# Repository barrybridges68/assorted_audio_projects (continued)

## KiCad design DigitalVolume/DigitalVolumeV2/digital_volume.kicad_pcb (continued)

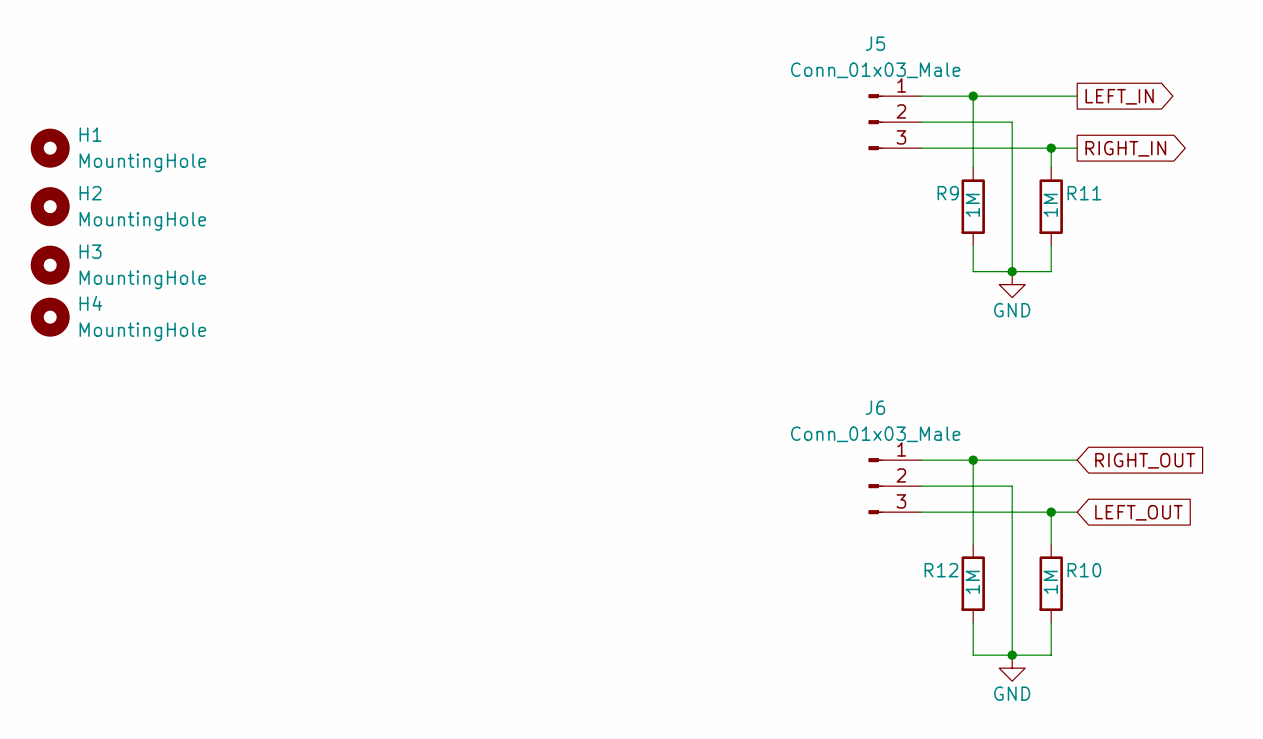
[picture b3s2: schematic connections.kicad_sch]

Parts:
H1, H2, H3, H4: MountingHole; MountingHole_3.2mm_M3
J5, J6: Conn_01x03_Male; TerminalBlock_Phoenix_MKDS-1,5-3-5.08_1x03_P5.08mm_Horizont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
R9, R10, R11, R12: 1M; R_0603_1608Metric

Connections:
GND: J5.2, J6.2, R9.2, R10.2, R11.2, R12.2; also elsewhere on the board
LEFT_IN: J5.1, R9.1; also elsewhere on the board
LEFT_OUT: J6.3, R10.1; also elsewhere on the board
RIGHT_IN: J5.3, R11.1; also elsewhere on the board
RIGHT_OUT: J6.1, R12.1; also elsewhere on the board

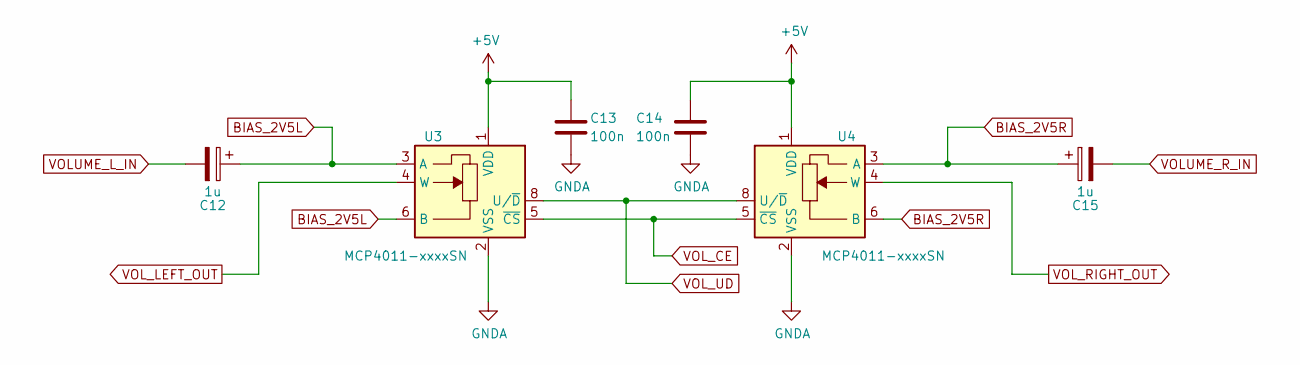
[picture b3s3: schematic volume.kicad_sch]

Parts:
C12, C15: 1u; CP_Elec_4x5.4
C13, C14: 100n; C_0603_1608Metric
U3, U4: MCP4011-xxxxSN; SOIC-8_3.9x4.9mm_P1.27mm

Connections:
+5V: C13.1, C14.1, U3.1 (VDD), U4.1 (VDD); also elsewhere on the board
BIAS_2V5L: C12.1, U3.3 (A), U3.6 (B); also elsewhere on the board
BIAS_2V5R: C15.1, U4.3 (A), U4.6 (B); also elsewhere on the board
GND: C13.2, C14.2, U3.2 (VSS), U4.2 (VSS); also elsewhere on the board
VOLUME_L_IN: C12.2; also elsewhere on the board
VOLUME_R_IN: C15.2; also elsewhere on the board
VOL_CE: U3.5 (~CS), U4.5 (~CS); also elsewhere on the board
VOL_LEFT_OUT: U3.4 (W); also elsewhere on the board
VOL_RIGHT_OUT: U4.4 (W); also elsewhere on the board
VOL_UD: U3.8 (U/~D), U4.8 (U/~D); also elsewhere on the board

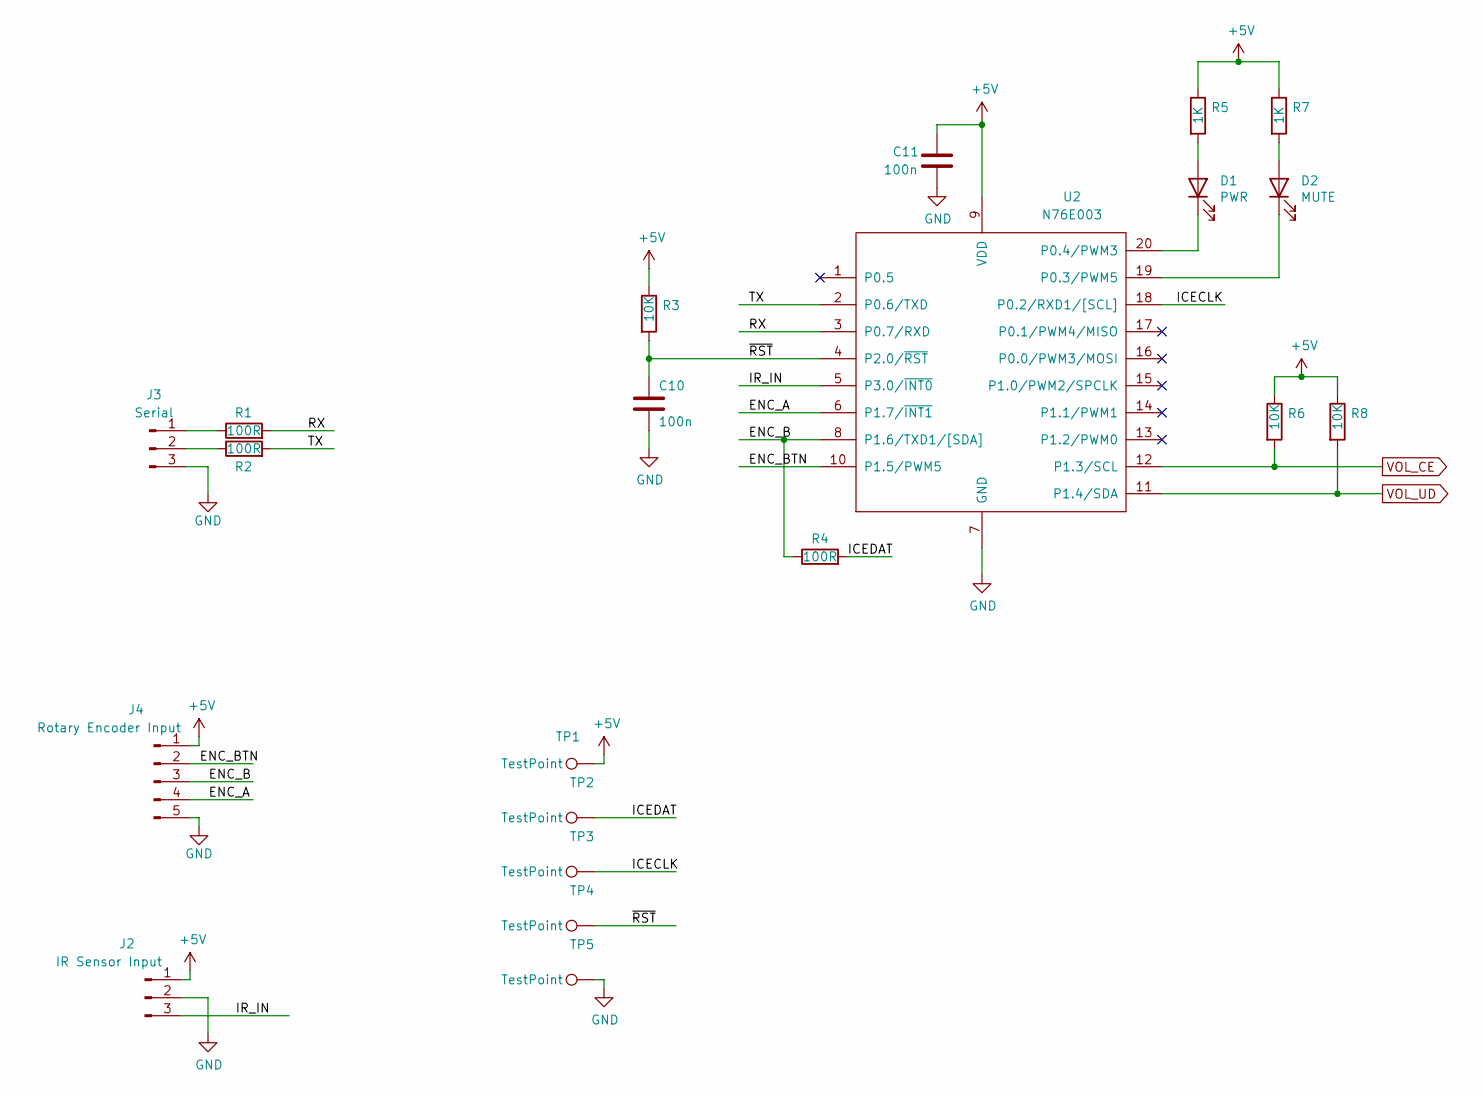
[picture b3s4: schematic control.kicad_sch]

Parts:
C10, C11: 100n; C_0603_1608Metric
D1: PWR; LED_0603_1608Metric_Pad1.05x0.95mm_HandSolder
D2: MUTE; LED_0603_1608Metric_Pad1.05x0.95mm_HandSolder
J2: IR Sensor Input; JST_EH_B3B-EH-A_1x03_P2.50mm_Vertical
J3: Serial; JST_EH_B3B-EH-A_1x03_P2.50mm_Vertical
J4: Rotary Encoder Input; JST_EH_B5B-EH-A_1x05_P2.50mm_Vertical
R1, R2, R4: 100R; R_0603_1608Metric
R3, R6, R8: 10K; R_0603_1608Metric
R5, R7: 1K; R_0603_1608Metric
TP1, TP2, TP3, TP4, TP5: TestPoint; TestPoint_Pad_1.0x1.0mm
U2: N76E003; TSSOP-20_4.4x6.5mm_P0.65mm

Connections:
+5V: C11.1, J2.1, J4.1, R3.1, R5.1, R6.1, R7.1, R8.1, TP1.1, U2.9 (VDD); also elsewhere on the board
/control/ENC_A: J4.4, U2.6 (P1.7/~INT1)
/control/ENC_B: J4.3, R4.1, U2.8 (P1.6/TXD1/[SDA])
/control/ENC_BTN: J4.2, U2.10 (P1.5/PWM5)
/control/ICECLK: TP3.1, U2.18 (P0.2/RXD1/[SCL])
/control/ICEDAT: R4.2, TP2.1
/control/IR_IN: J2.3, U2.5 (P3.0/~INT0)
/control/RX: R1.2, U2.3 (P0.7/RXD)
/control/TX: R2.2, U2.2 (P0.6/TXD)
/control/~RST: C10.1, R3.2, TP4.1, U2.4 (P2.0/~RST)
GND: C10.2, C11.2, J2.2, J3.3, J4.5, TP5.1, U2.7 (GND); also elsewhere on the board
unnamed: D1.1 (K), U2.20 (P0.4/PWM3)
unnamed: D1.2 (A), R5.2
unnamed: D2.1 (K), U2.19 (P0.3/PWM5)
unnamed: D2.2 (A), R7.2
unnamed: J3.1, R1.1
unnamed: J3.2, R2.1
VOL_CE: R6.2, U2.12 (P1.3/SCL); also elsewhere on the board
VOL_UD: R8.2, U2.11 (P1.4/SDA); also elsewhere on the board

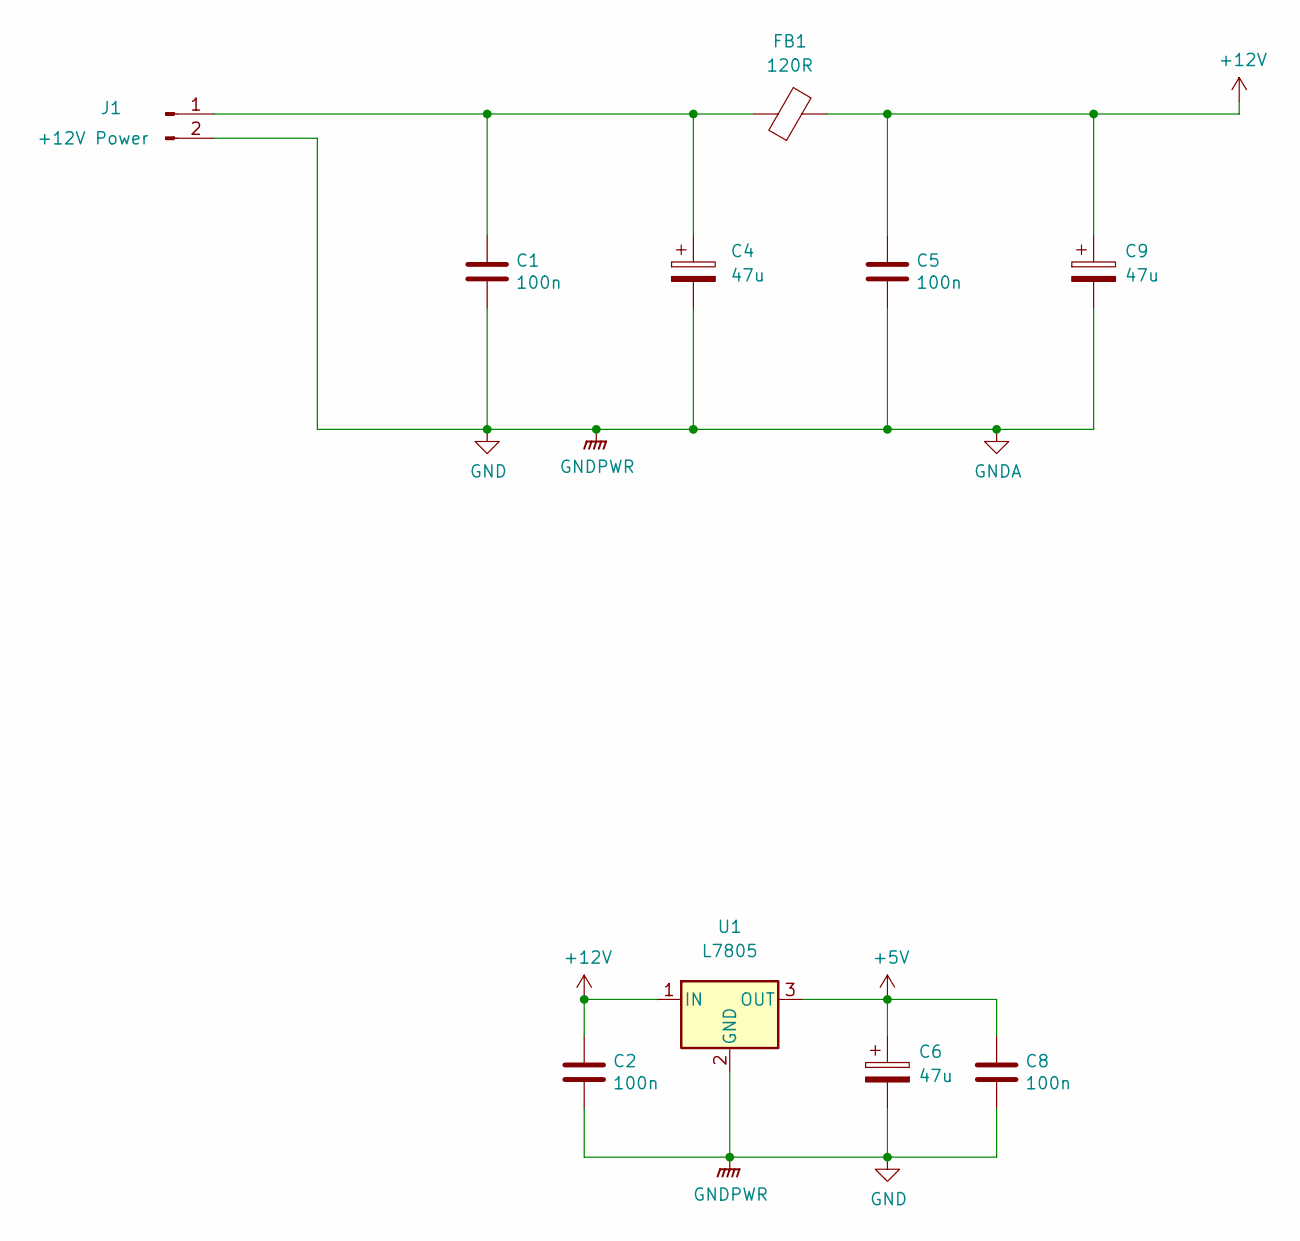
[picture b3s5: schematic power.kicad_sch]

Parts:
C1, C2, C5, C8: 100n; C_0603_1608Metric
C4, C6, C9: 47u; CP_Elec_6.3x5.3
FB1: 120R; R_0603_1608Metric
J1: +12V Power; TerminalBlock_Phoenix_MKDS-1,5-2_1x02_P5.00mm_Horizontal
U1: L7805; TO-252-2

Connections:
+5V: C6.1, C8.1, U1.3 (OUT); also elsewhere on the board
+12V: C2.1, C5.1, C9.1, FB1.2, U1.1 (IN); also elsewhere on the board
GND: C1.2, C2.2, C4.2, C5.2, C6.2, C8.2, C9.2, J1.2, U1.2 (GND); also elsewhere on the board
unnamed: C1.1, C4.1, FB1.1, J1.1

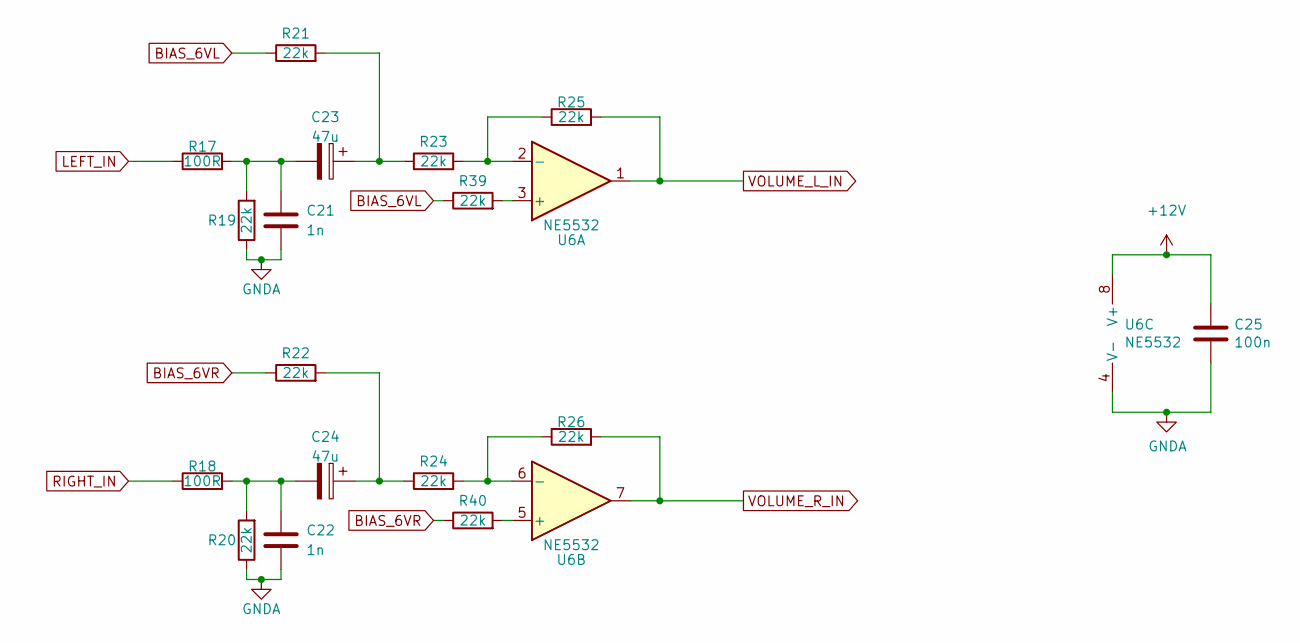
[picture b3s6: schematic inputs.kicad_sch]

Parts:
C21, C22: 1n; C_0603_1608Metric
C23, C24: 47u; CP_Elec_6.3x5.3
C25: 100n; C_0603_1608Metric
R17, R18: 100R; R_0603_1608Metric
R19, R20, R21, R22, R23, R24, R25, R26, R39, R40: 22k; R_0603_1608Metric
U6: NE5532; SOIC-8_3.9x4.9mm_P1.27mm

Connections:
+12V: C25.1, U6.8 (V+); also elsewhere on the board
BIAS_6VL: R21.1, R39.1; also elsewhere on the board
BIAS_6VR: R22.1, R40.1; also elsewhere on the board
GND: C21.2, C22.2, C25.2, R19.1, R20.1, U6.4 (V-); also elsewhere on the board
LEFT_IN: R17.1; also elsewhere on the board
unnamed: C21.1, C23.2, R17.2, R19.2
unnamed: C22.1, C24.2, R18.2, R20.2
unnamed: C23.1, R21.2, R23.1
unnamed: C24.1, R22.2, R24.1
unnamed: R23.2, R25.1, U6.2 (-)
unnamed: R24.2, R26.1, U6.6 (-)
unnamed: R39.2, U6.3 (+)
unnamed: R40.2, U6.5 (+)
RIGHT_IN: R18.1; also elsewhere on the board
VOLUME_L_IN: R25.2, U6.1; also elsewhere on the board
VOLUME_R_IN: R26.2, U6.7; also elsewhere on the board

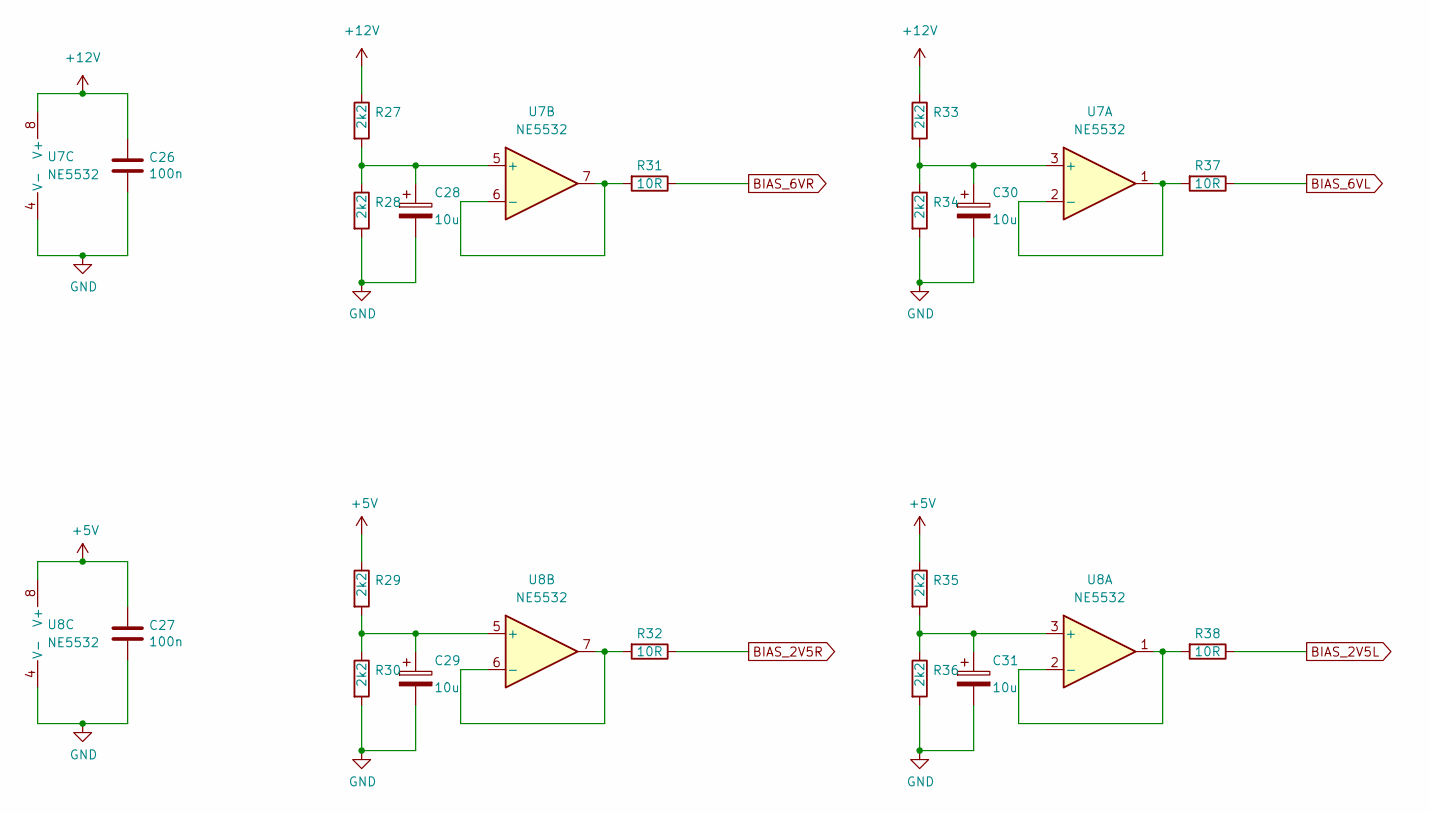
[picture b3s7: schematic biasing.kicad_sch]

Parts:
C26, C27: 100n; C_0603_1608Metric
C28, C29, C30, C31: 10u; CP_Elec_4x5.4
R27, R28, R29, R30, R33, R34, R35, R36: 2k2; R_0603_1608Metric
R31, R32, R37, R38: 10R; R_0603_1608Metric
U7, U8: NE5532; SOIC-8_3.9x4.9mm_P1.27mm

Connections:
+5V: C27.1, R29.1, R35.1, U8.8 (V+); also elsewhere on the board
+12V: C26.1, R27.1, R33.1, U7.8 (V+); also elsewhere on the board
BIAS_2V5L: R38.1; also elsewhere on the board
BIAS_2V5R: R32.1; also elsewhere on the board
BIAS_6VL: R37.1; also elsewhere on the board
BIAS_6VR: R31.1; also elsewhere on the board
GND: C26.2, C27.2, C28.2, C29.2, C30.2, C31.2, R28.2, R30.2, R34.2, R36.2, U7.4 (V-), U8.4 (V-); also elsewhere on the board
unnamed: C28.1, R27.2, R28.1, U7.5 (+)
unnamed: C29.1, R29.2, R30.1, U8.5 (+)
unnamed: C30.1, R33.2, R34.1, U7.3 (+)
unnamed: C31.1, R35.2, R36.1, U8.3 (+)
unnamed: R31.2, U7.6 (-), U7.7
unnamed: R32.2, U8.6 (-), U8.7
unnamed: R37.2, U7.1, U7.2 (-)
unnamed: R38.2, U8.1, U8.2 (-)

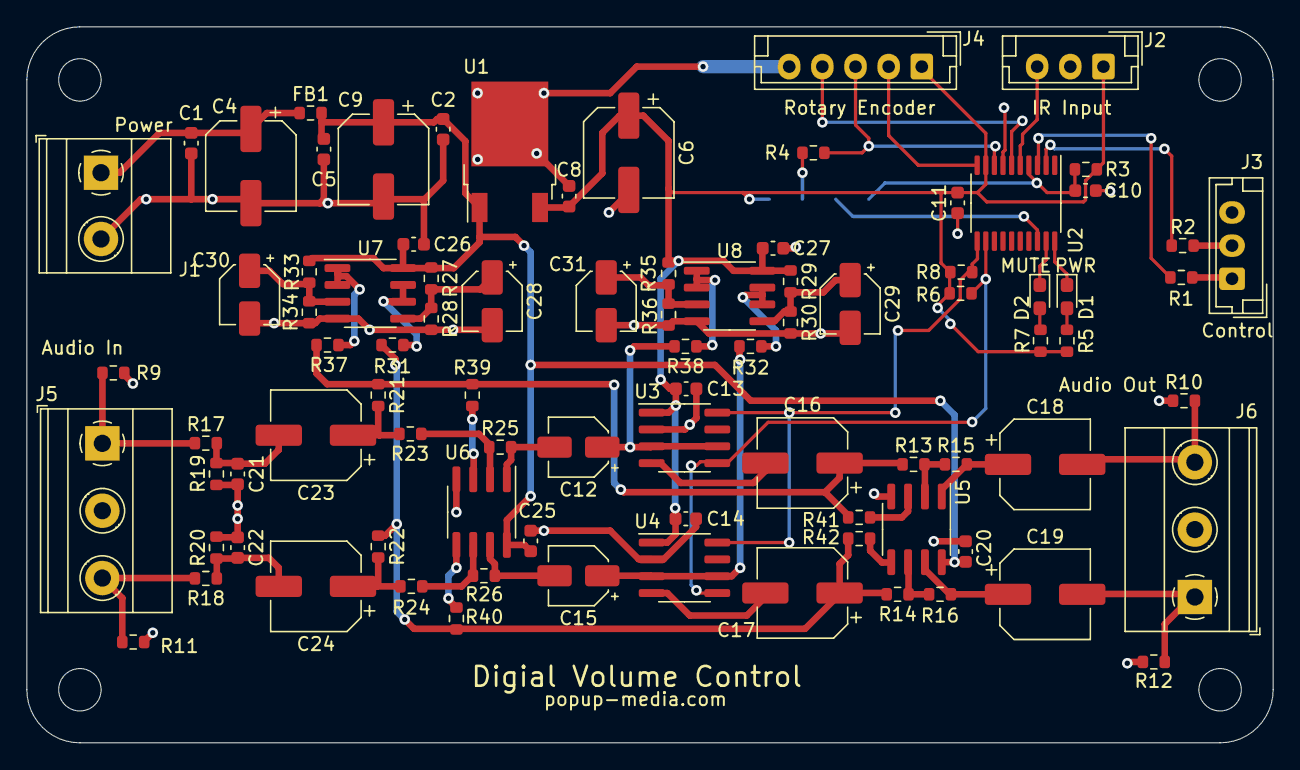
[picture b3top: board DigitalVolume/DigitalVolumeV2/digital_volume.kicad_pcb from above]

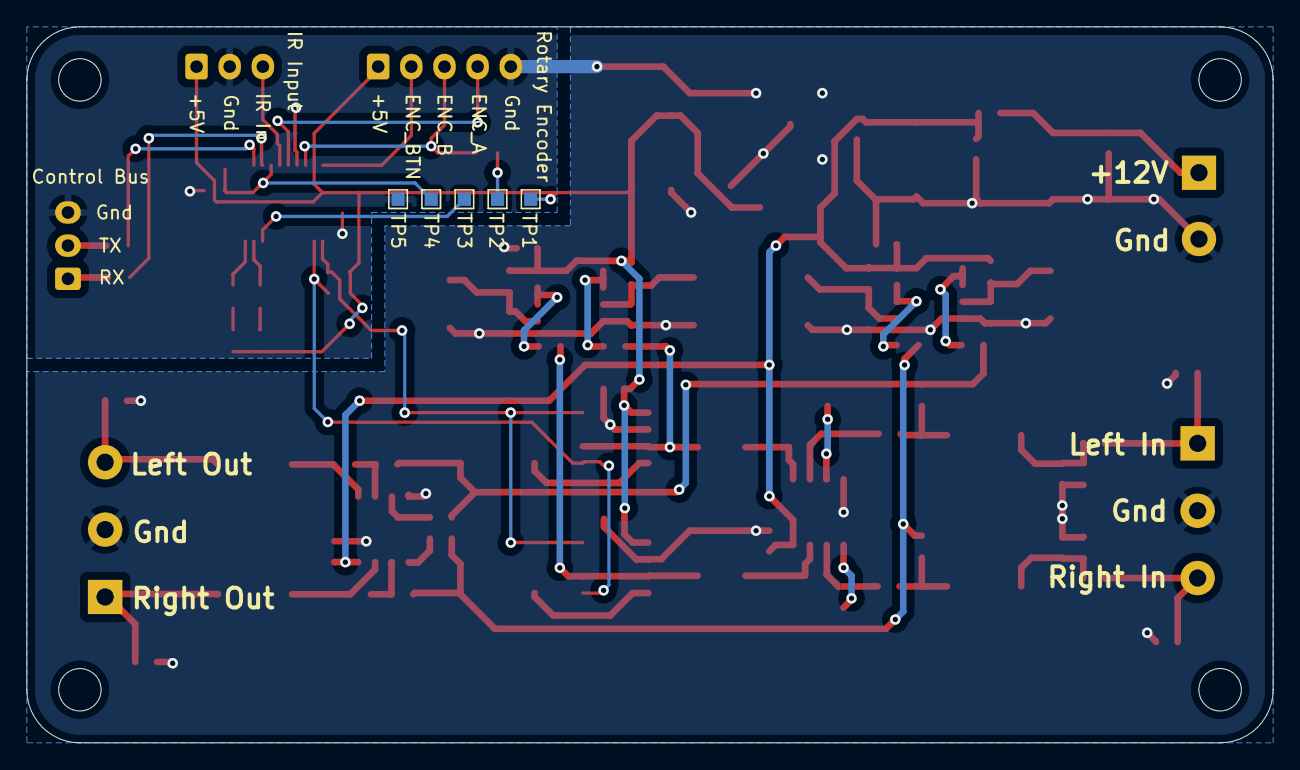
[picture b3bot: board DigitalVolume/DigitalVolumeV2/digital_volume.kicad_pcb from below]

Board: 2 copper layers, 94.0 x 54.0 mm, 97 parts (5 on the bottom side), 55 nets.

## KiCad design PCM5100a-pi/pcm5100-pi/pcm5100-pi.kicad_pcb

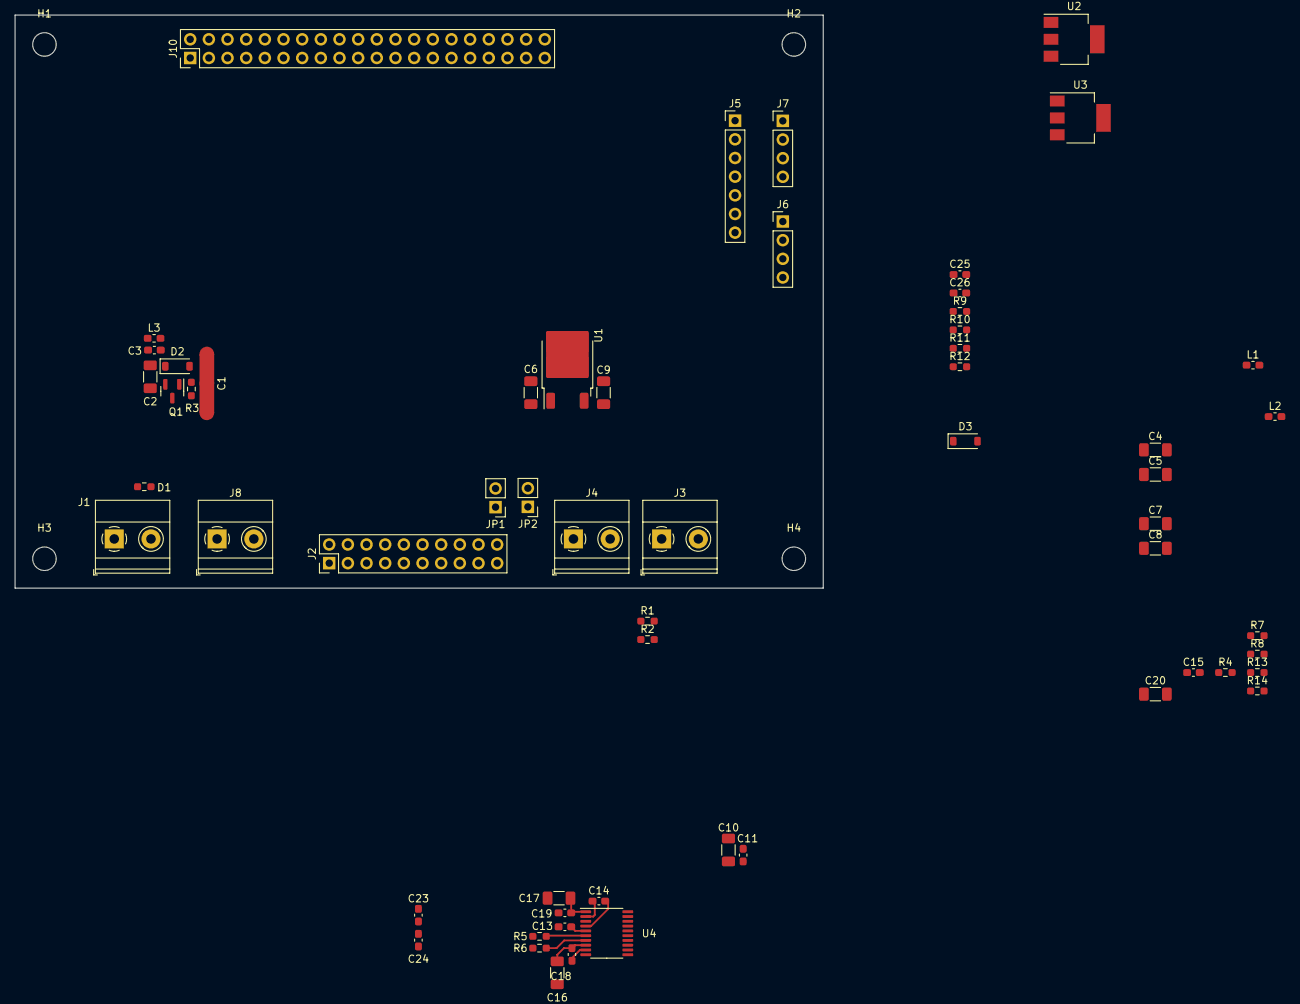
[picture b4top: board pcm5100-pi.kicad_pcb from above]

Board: 2 copper layers, 110.0 x 78.0 mm, 63 parts (0 on the bottom side), 58 nets.

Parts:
C1: 10u; NetTie-3_SMD_Pad2.0mm
C2, C7, C8, C9: 22u; C_1206_3216Metric_Pad1.33x1.80mm_HandSolder
C3, C11, C15, C18, C19, C25, C26: 100n; C_0603_1608Metric_Pad1.08x0.95mm_HandSolder
C4, C5, C6, C10, C16, C17, C20: 10u; C_1206_3216Metric_Pad1.33x1.80mm_HandSolder
C13, C14: 2u2; C_0603_1608Metric_Pad1.08x0.95mm_HandSolder
C23, C24: 2n2; C_0603_1608Metric_Pad1.08x0.95mm_HandSolder
D1: SLESDL0602; R_0603_1608Metric_Pad0.98x0.95mm_HandSolder
D2: BZT52C7V5; D_SOD-123
D3: 1N4148; D_SOD-123
H1, H2, H3, H4: MountingHole; MountingHole_3.2mm_M3
J1: Power; TerminalBlock_Phoenix_MKDS-1,5-2_1x02_P5.00mm_Horizontal
J2: GPIO Port; PinHeader_2x10_P2.54mm_Vertical
J3: Audio Right Out; TerminalBlock_Phoenix_MKDS-1,5-2_1x02_P5.00mm_Horizontal
J4: Audio Left Out; TerminalBlock_Phoenix_MKDS-1,5-2_1x02_P5.00mm_Horizontal
J5: SPI Port; PinHeader_1x07_P2.54mm_Vertical
J6: PWM Port; PinHeader_1x04_P2.54mm_Vertical
J7: I2C Port; PinHeader_1x04_P2.54mm_Vertical
J8: Control; TerminalBlock_Phoenix_MKDS-1,5-2_1x02_P5.00mm_Horizontal
J10: Raspberry_Pi_2_3; PinHeader_2x20_P2.54mm_Vertical
JP1: SDA; PinHeader_1x02_P2.54mm_Vertical
JP2: SCL; PinHeader_1x02_P2.54mm_Vertical
L1, L2, L3: L_Ferrite; L_0603_1608Metric_Pad1.05x0.95mm_HandSolder
Q1: SSM3J338R,LF; SOT-23
R1, R2, R3: 100k; R_0603_1608Metric_Pad0.98x0.95mm_HandSolder
R4: 10k; R_0603_1608Metric_Pad0.98x0.95mm_HandSolder
R5, R6: 470R; R_0603_1608Metric_Pad0.98x0.95mm_HandSolder
R7, R8, R13, R14: 0R; R_0603_1608Metric_Pad0.98x0.95mm_HandSolder
R9: 10R; R_0603_1608Metric_Pad0.98x0.95mm_HandSolder
R10: 1k; R_0603_1608Metric_Pad0.98x0.95mm_HandSolder
R11, R12: 4k7; R_0603_1608Metric_Pad0.98x0.95mm_HandSolder
U1: L7805; TO-252-2
U2, U3: AMS1117-3.3; SOT-223-3_TabPin2
U4: PCM5100; TSSOP-20_4.4x6.5mm_P0.65mm

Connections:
+3.3VA: C7.1, C16.1, C18.1, U2.2 (VO), U4.8 (AVDD)
+3V3: C8.1, C10.1, C11.1, J2.1, J2.20, J5.1, J6.1, J7.1, U3.2 (VO), U4.20 (DVDD)
+5V: C9.1, C25.1, C26.1, J2.9, J2.10, J10.2 (5V), J10.4 (5V), U1.3 (OUT)
+12V: C2.1, C3.1, D2.1 (K), L1.1, L2.1, L3.1, Q1.2 (S)
/Audio/CPGND: C13.2, C17.2, C19.2, U4.3 (CPGND)
/Audio/OUTL: R5.1, U4.6 (OUTL)
/Audio/OUTR: R6.1, U4.7 (OUTR)
AUDIO_L_OUT: C23.1, J4.1, R2.1, R5.2
AUDIO_R_OUT: C24.1, J3.1, R1.1, R6.2
BCK: J10.12 (GPIO18/PWM0), U4.13 (BCK)
CTRL: J8.1, R9.2, R10.1
DIN: J10.40 (GPIO21/SCLK1), U4.14 (DIN)
GND: C1.2, C2.2, C3.2, C6.2, C9.2, D1.1 (A1), R3.2, U1.2 (GND)
GNDA: C4.2, C7.2, C16.2, C18.2, C23.2, C24.2, J1.1, J3.2, J4.2, R1.2, R2.2, U2.1 (GND), U4.9 (AGND)
GNDD: C5.2, C8.2, C10.2, C11.2, C15.2, C20.2, C25.2, C26.2, J2.11, J2.12, J5.7, J6.4, J7.4, J8.2, J10.6 (GND), J10.9 (GND), J10.14 (GND), J10.20 (GND), J10.25 (GND), J10.30 (GND), J10.34 (GND), J10.39 (GND), R4.2, R13.1, R14.1, U3.1 (GND), U4.16 (FMT), U4.19 (DGND)
GPIO_00: J2.2, J10.27 (ID_SD/GPIO0), R8.1
GPIO_01: J2.3, J10.28 (ID_SC/GPIO1), R7.1
GPIO_04: J2.4, J10.7 (GCLK0/GPIO4)
GPIO_05: J2.5, J10.29 (GCLK1/GPIO5)
GPIO_06: J2.6, J10.31 (GCLK2/GPIO6)
GPIO_16: J2.7, J10.36 (GPIO16)
GPIO_17: J2.8, J10.11 (GPIO17)
GPIO_20: J2.19, J10.38 (GPIO20/MOSI1)
GPIO_22: J2.18, J10.15 (GPIO22)
GPIO_23: J2.17, J10.16 (GPIO23)
GPIO_24: J2.16, J10.18 (GPIO24)
GPIO_25: J2.15, J10.22 (GPIO25)
GPIO_26: J2.14, J10.37 (GPIO26)
GPIO_27: J2.13, J10.13 (GPIO27)
MISO: J5.4, J10.21 (MISO0/GPIO9)
MOSI: J5.5, J10.19 (MOSI0/GPIO10)
unnamed: C1.1, D2.2 (A), Q1.1 (G), R3.1
unnamed: D3.2 (A), R9.1
unnamed: D3.1 (K), J10.8 (GPIO14/TXD)
unnamed: J10.10 (GPIO15/RXD), R10.2
unnamed: JP1.1 (A), R11.1
unnamed: J10.1 (3V3), J10.17 (3V3), JP1.2 (B), JP2.2 (B)
unnamed: JP2.1 (A), R12.1
unnamed: C6.1, L3.2, U1.1 (IN)
unnamed: C4.1, L1.2, U2.3 (VI)
unnamed: C5.1, L2.2, U3.3 (VI)
unnamed: C14.2, U4.4 (CAPM)
unnamed: C14.1, U4.2 (CAPP)
unnamed: C17.1, C19.1, U4.1 (CPVDD)
unnamed: R8.2, R14.2, U4.10 (DEMP)
unnamed: R7.2, R13.2, U4.11 (FLT)
unnamed: C15.1, C20.1, U4.18 (LDOO)
unnamed: C13.1, U4.5 (VNEG)
POWER_RAW_12V: D1.2 (A2), J1.2, Q1.3 (D)
PWM0: J6.2, J10.32 (PWM0/GPIO12)
PWM1: J6.3, J10.33 (PWM1/GPIO13)
RLCLK: J10.35 (GPIO19/MISO1), U4.15 (LRCK)
SCL: J7.3, J10.5 (SCL/GPIO3), R12.2
SCLK: J5.6, J10.23 (SCLK0/GPIO11), U4.12 (SCK)
SDA: J7.2, J10.3 (SDA/GPIO2), R11.2
~CE0: J5.3, J10.24 (~CE0/GPIO8)
~CE1: J5.2, J10.26 (~CE1/GPIO7)
~MUTE: R4.1, U4.17 (XSMT)

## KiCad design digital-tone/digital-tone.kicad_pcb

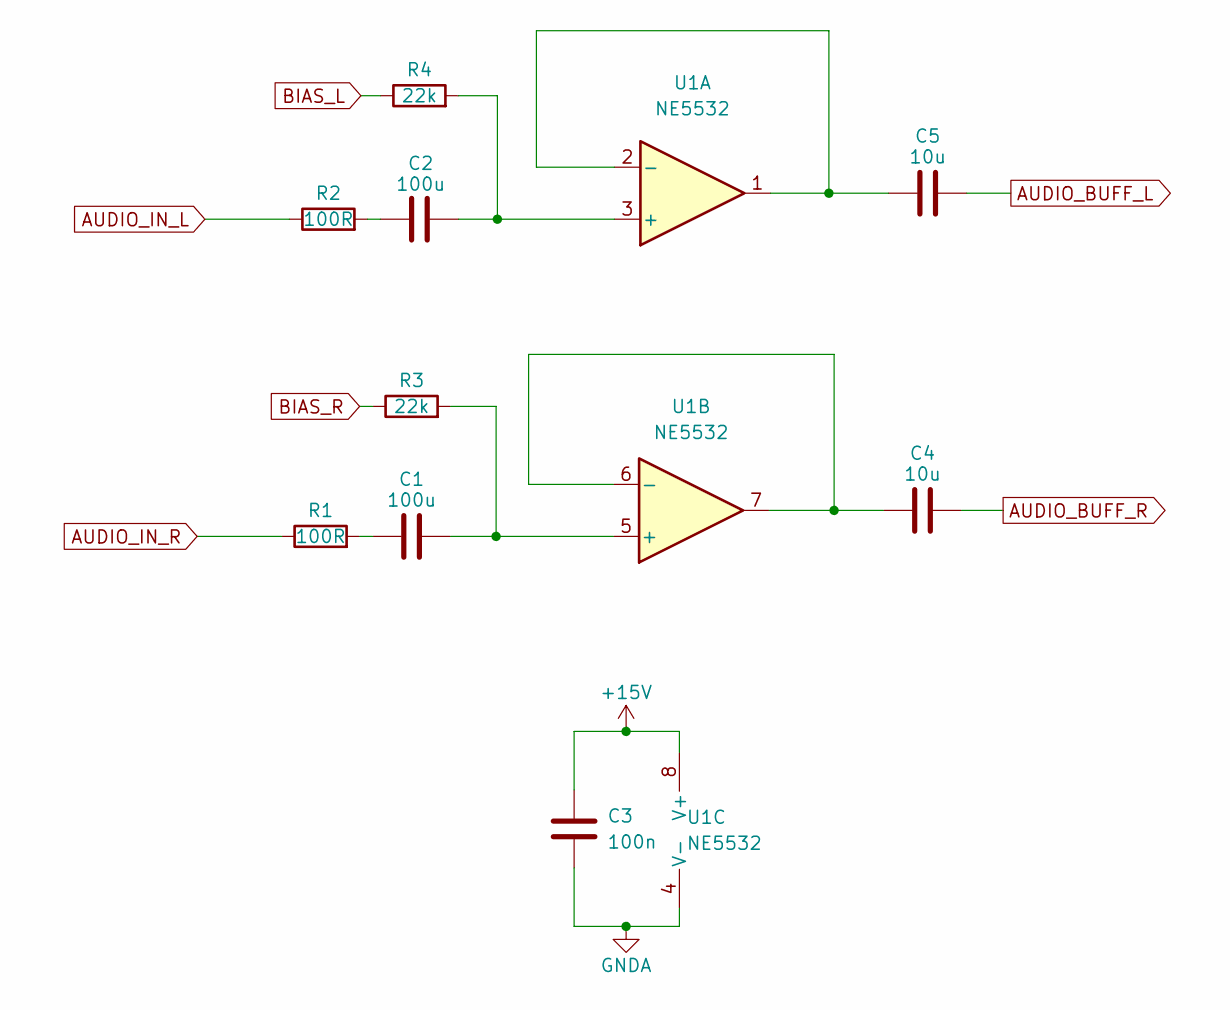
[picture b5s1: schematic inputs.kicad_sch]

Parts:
C1, C2: 100u; C_1206_3216Metric
C3: 100n; C_0603_1608Metric_Pad1.08x0.95mm_HandSolder
C4, C5: 10u; C_0603_1608Metric_Pad1.08x0.95mm_HandSolder
R1, R2: 100R; R_0603_1608Metric_Pad0.98x0.95mm_HandSolder
R3, R4: 22k; R_0603_1608Metric_Pad0.98x0.95mm_HandSolder
U1: NE5532; SOIC-8_3.9x4.9mm_P1.27mm

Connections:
+15V: C3.1, U1.8 (V+); also elsewhere on the board
AUDIO_BUFF_L: C5.2; also elsewhere on the board
AUDIO_BUFF_R: C4.2; also elsewhere on the board
AUDIO_IN_L: R2.1; also elsewhere on the board
AUDIO_IN_R: R1.1; also elsewhere on the board
BIAS_L: R4.1; also elsewhere on the board
BIAS_R: R3.1; also elsewhere on the board
unnamed: C1.1, R1.2
unnamed: C1.2, R3.2, U1.5 (+)
unnamed: C2.1, R2.2
unnamed: C2.2, R4.2, U1.3 (+)
unnamed: C4.1, U1.6 (-), U1.7
unnamed: C5.1, U1.1, U1.2 (-)

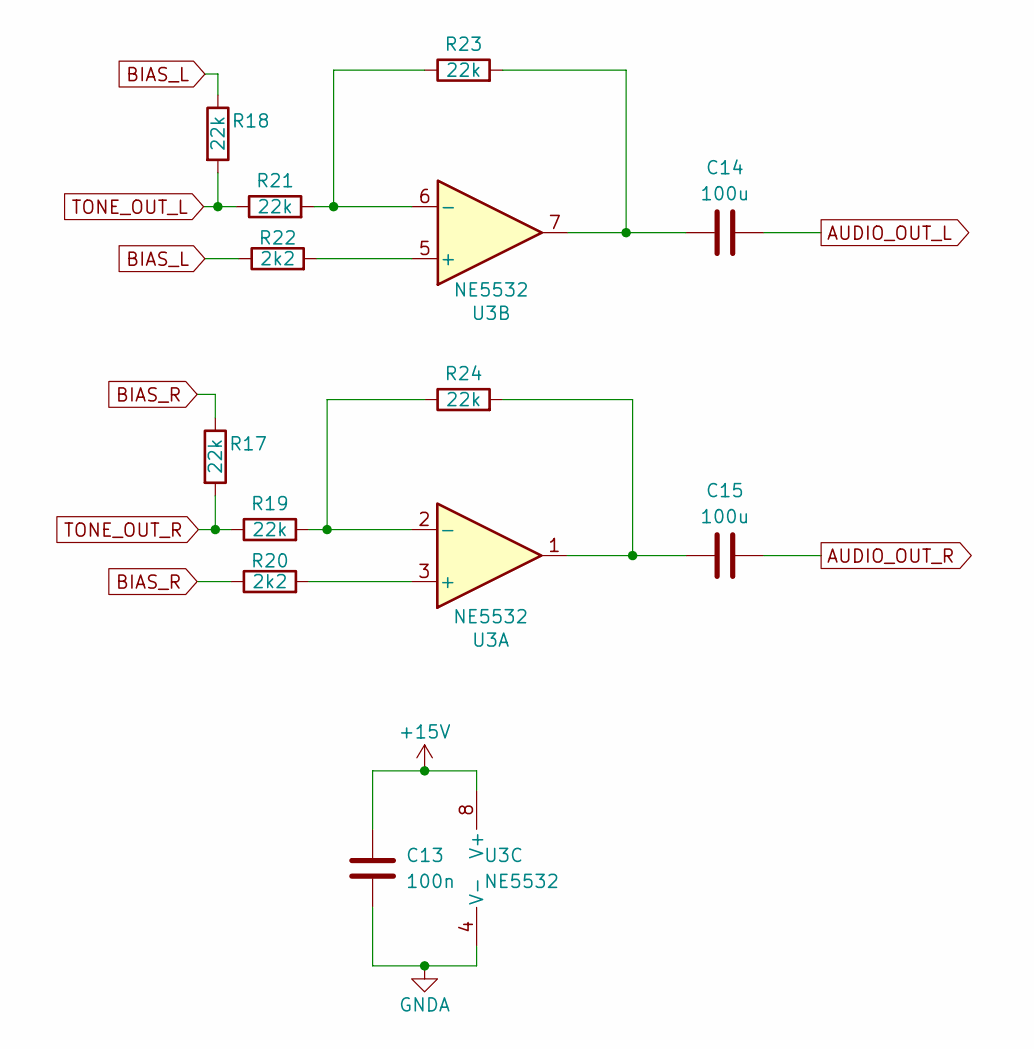
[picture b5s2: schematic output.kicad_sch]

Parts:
C13: 100n; C_0603_1608Metric_Pad1.08x0.95mm_HandSolder
C14, C15: 100u; C_1206_3216Metric_Pad1.33x1.80mm_HandSolder
R17, R18, R19, R21, R23, R24: 22k; R_0603_1608Metric_Pad0.98x0.95mm_HandSolder
R20, R22: 2k2; R_0603_1608Metric_Pad0.98x0.95mm_HandSolder
U3: NE5532; SOIC-8_3.9x4.9mm_P1.27mm

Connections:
+15V: C13.1, U3.8 (V+); also elsewhere on the board
AUDIO_OUT_L: C14.2; also elsewhere on the board
AUDIO_OUT_R: C15.2; also elsewhere on the board
BIAS_L: R18.1, R22.1; also elsewhere on the board
BIAS_R: R17.1, R20.1; also elsewhere on the board
unnamed: C14.1, R23.2, U3.7
unnamed: C15.1, R24.2, U3.1
unnamed: R19.2, R24.1, U3.2 (-)
unnamed: R20.2, U3.3 (+)
unnamed: R21.2, R23.1, U3.6 (-)
unnamed: R22.2, U3.5 (+)
TONE_OUT_L: R18.2, R21.1; also elsewhere on the board
TONE_OUT_R: R17.2, R19.1; also elsewhere on the board

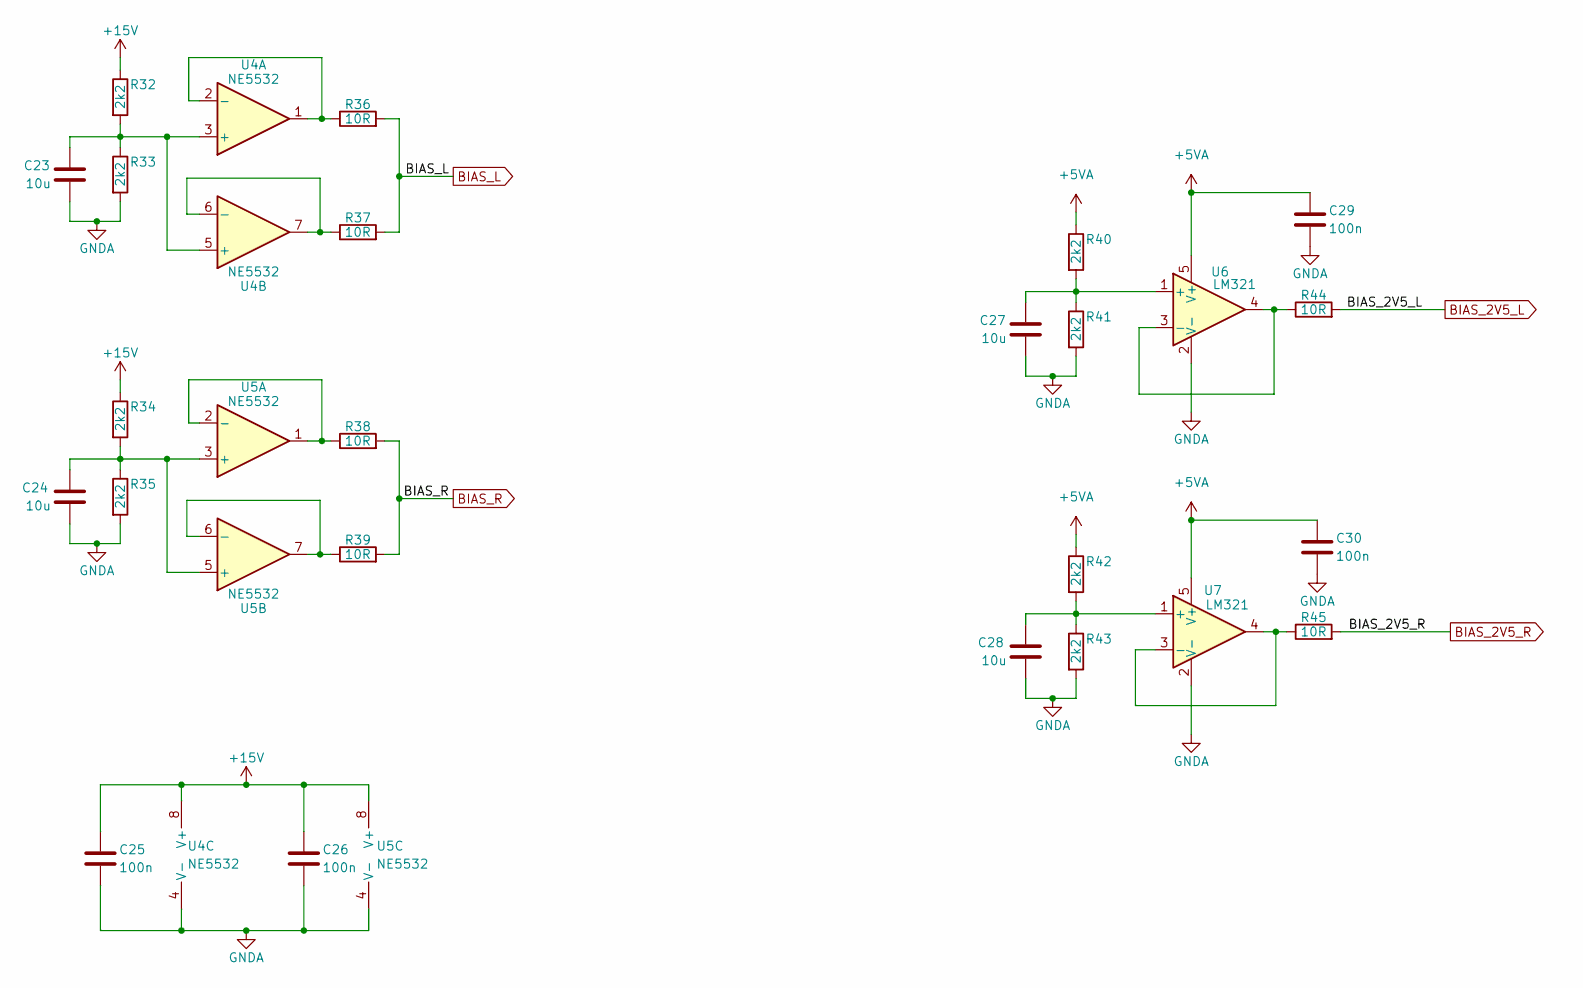
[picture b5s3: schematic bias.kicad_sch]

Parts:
C23, C24, C27, C28: 10u; C_0603_1608Metric_Pad1.08x0.95mm_HandSolder
C25, C26, C29, C30: 100n; C_0603_1608Metric_Pad1.08x0.95mm_HandSolder
R32, R33, R34, R35, R40, R41, R42, R43: 2k2; R_0603_1608Metric_Pad0.98x0.95mm_HandSolder
R36, R37, R38, R39, R44, R45: 10R; R_0603_1608Metric_Pad0.98x0.95mm_HandSolder
U4, U5: NE5532; SOIC-8_3.9x4.9mm_P1.27mm
U6, U7: LM321; SOT-23-5

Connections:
+5VA: C29.1, C30.1, R40.1, R42.1, U6.5 (V+), U7.5 (V+); also elsewhere on the board
+15V: C25.1, C26.1, R32.1, R34.1, U4.8 (V+), U5.8 (V+); also elsewhere on the board
BIAS_2V5_L: R44.2; also elsewhere on the board
BIAS_2V5_R: R45.2; also elsewhere on the board
BIAS_L: R36.2, R37.2; also elsewhere on the board
BIAS_R: R38.2, R39.2; also elsewhere on the board
unnamed: C23.1, R32.2, R33.1, U4.3 (+), U4.5 (+)
unnamed: C24.1, R34.2, R35.1, U5.3 (+), U5.5 (+)
unnamed: C27.1, R40.2, R41.1, U6.1 (+)
unnamed: C28.1, R42.2, R43.1, U7.1 (+)
unnamed: R36.1, U4.1, U4.2 (-)
unnamed: R37.1, U4.6 (-), U4.7
unnamed: R38.1, U5.1, U5.2 (-)
unnamed: R39.1, U5.6 (-), U5.7
unnamed: R44.1, U6.3 (-), U6.4
unnamed: R45.1, U7.3 (-), U7.4
